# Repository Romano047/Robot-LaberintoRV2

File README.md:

# Robot-LaberintoRV2
Robot Laberinto R 2024-2025

Proyecto realizado en la Escuela de Educación Secundaria Técnica N°5 "2 de Abril" Temperley, Buenos Aires, Argentina. Desarrollado por Iván Romano, estudiante de Electrónica de la institución a cargo del profesor Ing. Martín Leguizamón.

El objetivo de este reoositrio es el de desarrollar un robot autónomo de competición dentro de la categoría de "Robot Laberinto". 

Se tomarán como referencia en su elaboración las reglas actualmente vigentes (2024) dentro de la Liga Nacional de Robótica (LNR) en la categoría de "Laberinto". 

# Guía de Repositorio

- Hardware
  - KiCad: En ella se encuentran todos los archivos correspondientes al desarrollo del PCB.

- 3D
  - AutoCad: En esta carpeta se encuentran los archivos correspondientes al diseño 3D en conjunto a sus trazados a formato .stl para facilitar su posterior impresión. 

- Software
  - Ensayos: Ensayos básicos de cada funcionalidad o punto de interés de forma aislada que conforman el robot. (A su vez se encontrarán en el archivos correspondientes al robort de competición provincial "Alita").
  - LaberintoR2_v2: Versión del Software ejecutada actualmente en el robot. 

# Especificaciones

- Software: Desarrollado en C Orientado a Objetos, por medio del uso de VsCode en conjunto a su extensión PlatformIO.
- Desarrollo de PCBs: KiCad 7
- Placa de Desarrollo: Espressif ESP-32 WROOM DEV KIT
- Sensores de proximidad: HC-SR04
- Drivers de Motores: TB6612fng

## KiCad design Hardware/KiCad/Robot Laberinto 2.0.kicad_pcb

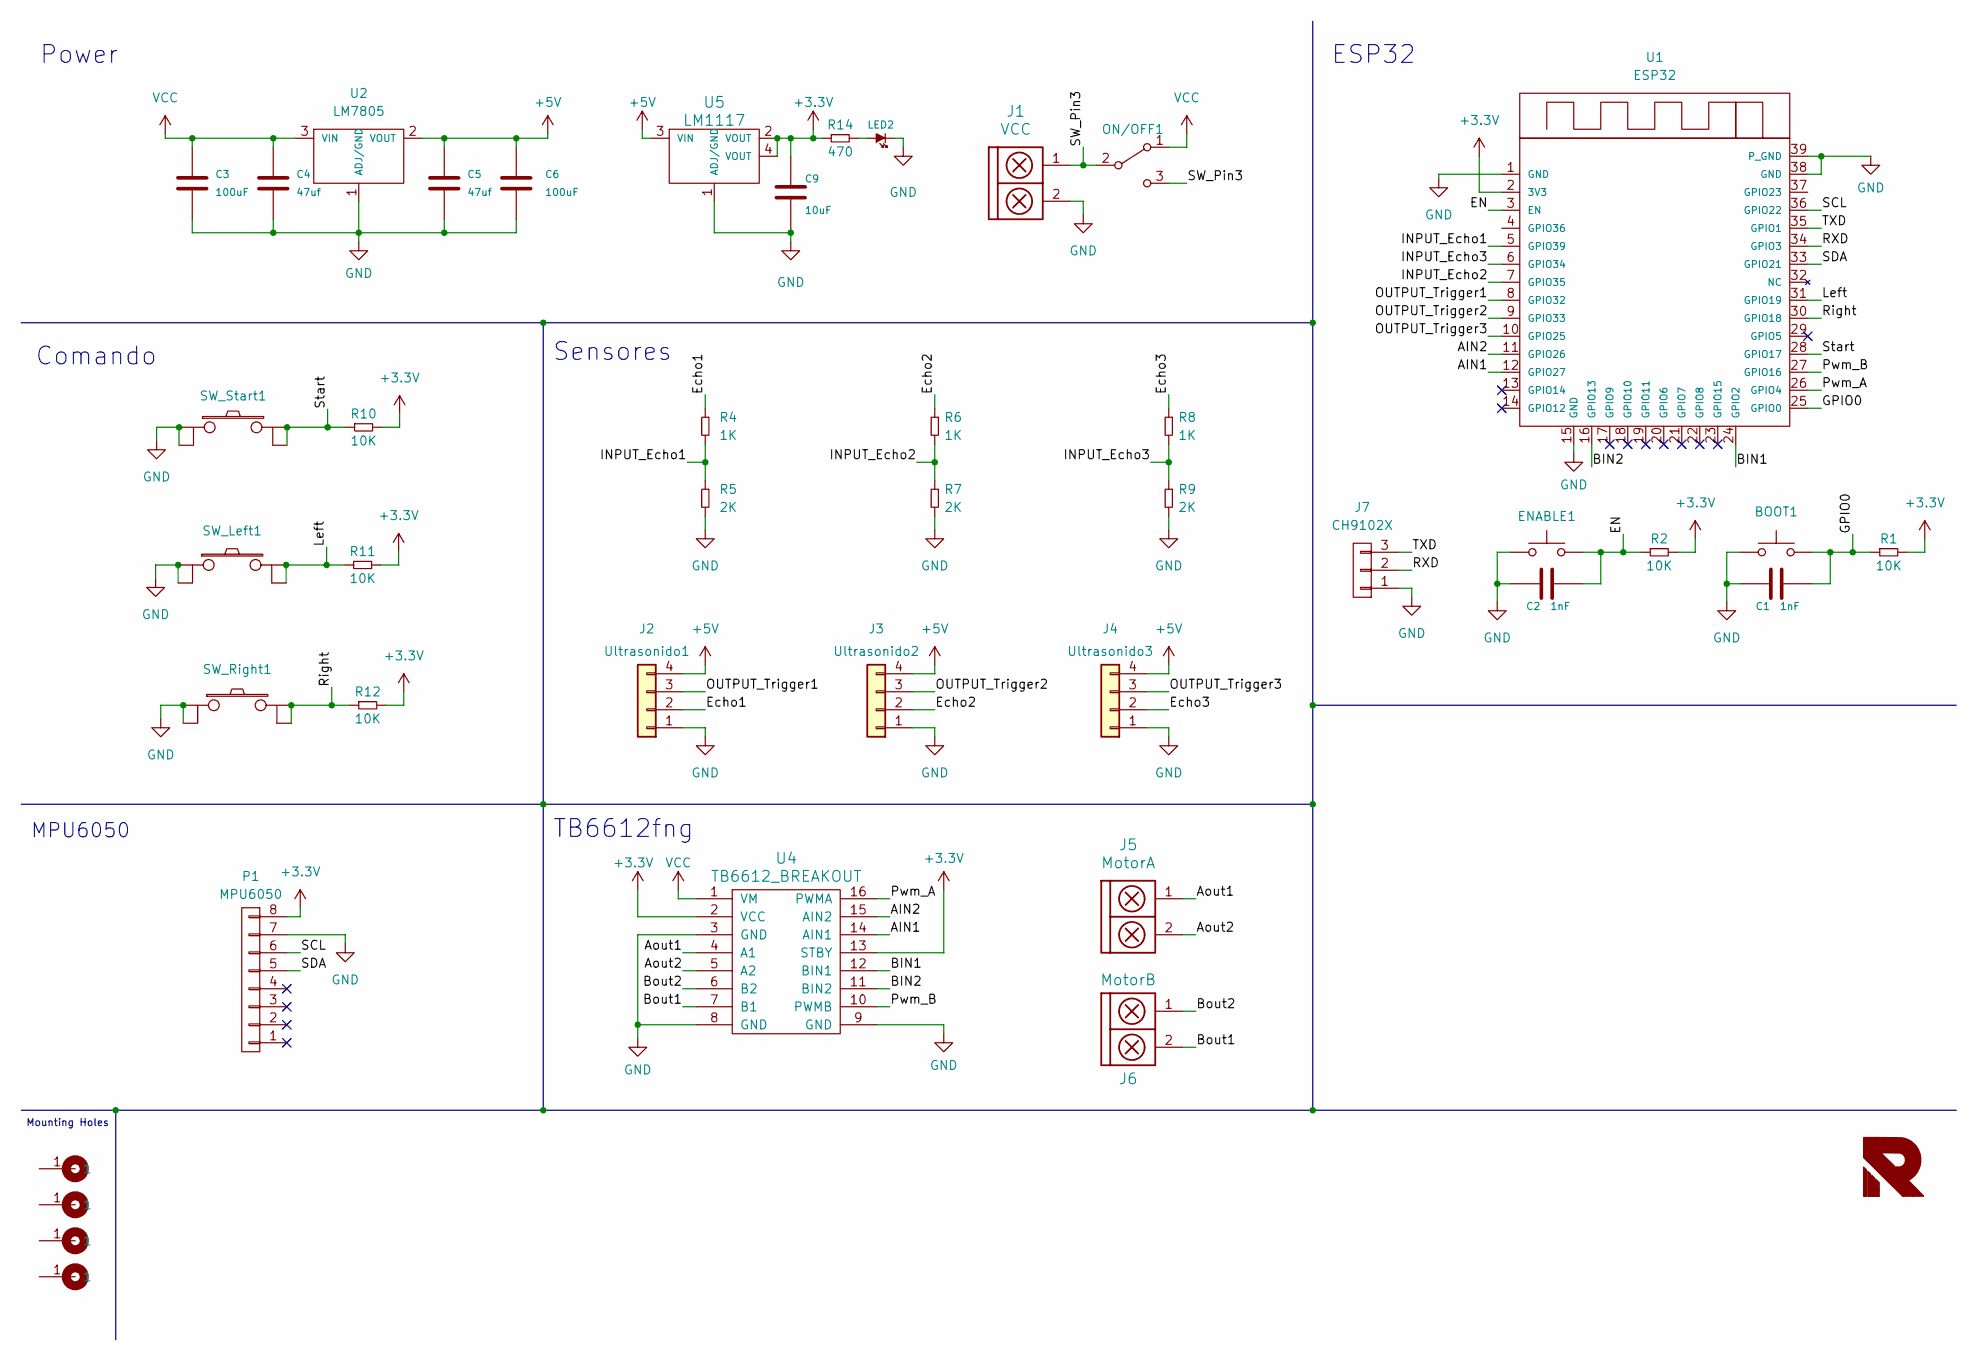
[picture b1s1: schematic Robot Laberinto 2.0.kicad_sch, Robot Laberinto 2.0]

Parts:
BOOT1: SW_Push; SW_SPST_EVQPE1
C1, C2: 1nF; C_0805
C3, C6: 100uF; CAP_ELEC_5x11mm
C4, C5: 47uf; C_0805
C9: 10uF; CAP_ELEC_5x11mm
ENABLE1: SW_Push; SW_SPST_EVQPE1
J1: VCC; BORNERA2_AZUL
J2: Ultrasonido1; pin_strip_4
J3: Ultrasonido2; pin_strip_4
J4: Ultrasonido3; pin_strip_4
J5: MotorA; BORNERA2_AZUL
J6: MotorB; BORNERA2_AZUL
J7: CH9102X; Pin_Strip_3
J8, J9, J10, J11: Cable_PAD; Separador_M3_5mm
LED2: LED; Led_0805
ON/OFF1: SW_SPDT; SW_SPDT_TH_Vertical
P1: MPU6050; Pin_Header_Straight_1x08
R1, R2, R10, R11, R12: 10K; R_0805
R4, R6, R8: 1K; R_0805
R5, R7, R9: 2K; R_0805
R14: 470; R_0805
SW_Left1: SW_PUSH; PUSH_SWITCH_THT
SW_Right1: SW_PUSH; PUSH_SWITCH_THT
SW_Start1: SW_PUSH; PUSH_SWITCH_THT
U1: ESP32; ESP32-WROOM-32_MacroLib
U2: LM7805; TO-220
U4: TB6612_BREAKOUT; TB6612_Breakout
U5: LM1117; SOT223

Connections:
+3.3V: C9.1, P1.8, R1.2, R2.2, R10.2, R11.2, R12.2, R14.1, U1.2 (3V3), U4.2 (VCC), U4.13 (STBY), U5.2 (VOUT), U5.4 (VOUT)
+5V: C5.1, C6.1, J2.4, J3.4, J4.4, U2.2 (VOUT), U5.3 (VIN)
/AIN1: U1.12 (GPIO27), U4.14 (AIN1)
/AIN2: U1.11 (GPIO26), U4.15 (AIN2)
/Aout1: J5.1, U4.4 (A1)
/Aout2: J5.2, U4.5 (A2)
/BIN1: U1.24 (GPIO2), U4.12 (BIN1)
/BIN2: U1.16 (GPIO13), U4.11 (BIN2)
/Bout1: J6.2, U4.7 (B1)
/Bout2: J6.1, U4.6 (B2)
/EN: C2.2, ENABLE1.2, R2.1, U1.3 (EN)
/Echo1: J2.2, R4.1
/Echo2: J3.2, R6.1
/Echo3: J4.2, R8.1
/GPIO0: BOOT1.2, C1.2, R1.1, U1.25 (GPIO0)
/INPUT_Echo1: R4.2, R5.1, U1.5 (GPIO39)
/INPUT_Echo2: R6.2, R7.1, U1.7 (GPIO35)
/INPUT_Echo3: R8.2, R9.1, U1.6 (GPIO34)
/Left: R11.1, SW_Left1.3, SW_Left1.4, U1.31 (GPIO19)
/OUTPUT_Trigger1: J2.3, U1.8 (GPIO32)
/OUTPUT_Trigger2: J3.3, U1.9 (GPIO33)
/OUTPUT_Trigger3: J4.3, U1.10 (GPIO25)
/Pwm_A: U1.26 (GPIO4), U4.16 (PWMA)
/Pwm_B: U1.27 (GPIO16), U4.10 (PWMB)
/RXD: J7.2, U1.34 (GPIO3)
/Right: R12.1, SW_Right1.3, SW_Right1.4, U1.30 (GPIO18)
/SCL: P1.6, U1.36 (GPIO22)
/SDA: P1.5, U1.33 (GPIO21)
/SW_Pin3: J1.1, ON/OFF1.2 (B), ON/OFF1.3 (C)
/Start: R10.1, SW_Start1.3, SW_Start1.4, U1.28 (GPIO17)
/TXD: J7.3, U1.35 (GPIO1)
GND: BOOT1.1, C1.1, C2.1, C3.2, C4.2, C5.2, C6.2, C9.2, ENABLE1.1, J1.2, J2.1, J3.1, J4.1, J7.1, LED2.2 (K), P1.7, R5.2, R7.2, R9.2, SW_Left1.1, SW_Left1.2, SW_Right1.1, SW_Right1.2, SW_Start1.1, SW_Start1.2, U1.1 (GND), U1.15 (GND), U1.38 (GND), U1.39 (P_GND), U2.1 (ADJ/GND), U4.3 (GND), U4.8 (GND), U4.9 (GND), U5.1 (ADJ/GND)
unnamed: LED2.1 (A), R14.2
VCC: C3.1, C4.1, ON/OFF1.1 (A), U2.3 (VIN), U4.1 (VM)

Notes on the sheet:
Sensores
Comando
Mounting Holes
MPU6050
TB6612fng
ESP32
Power

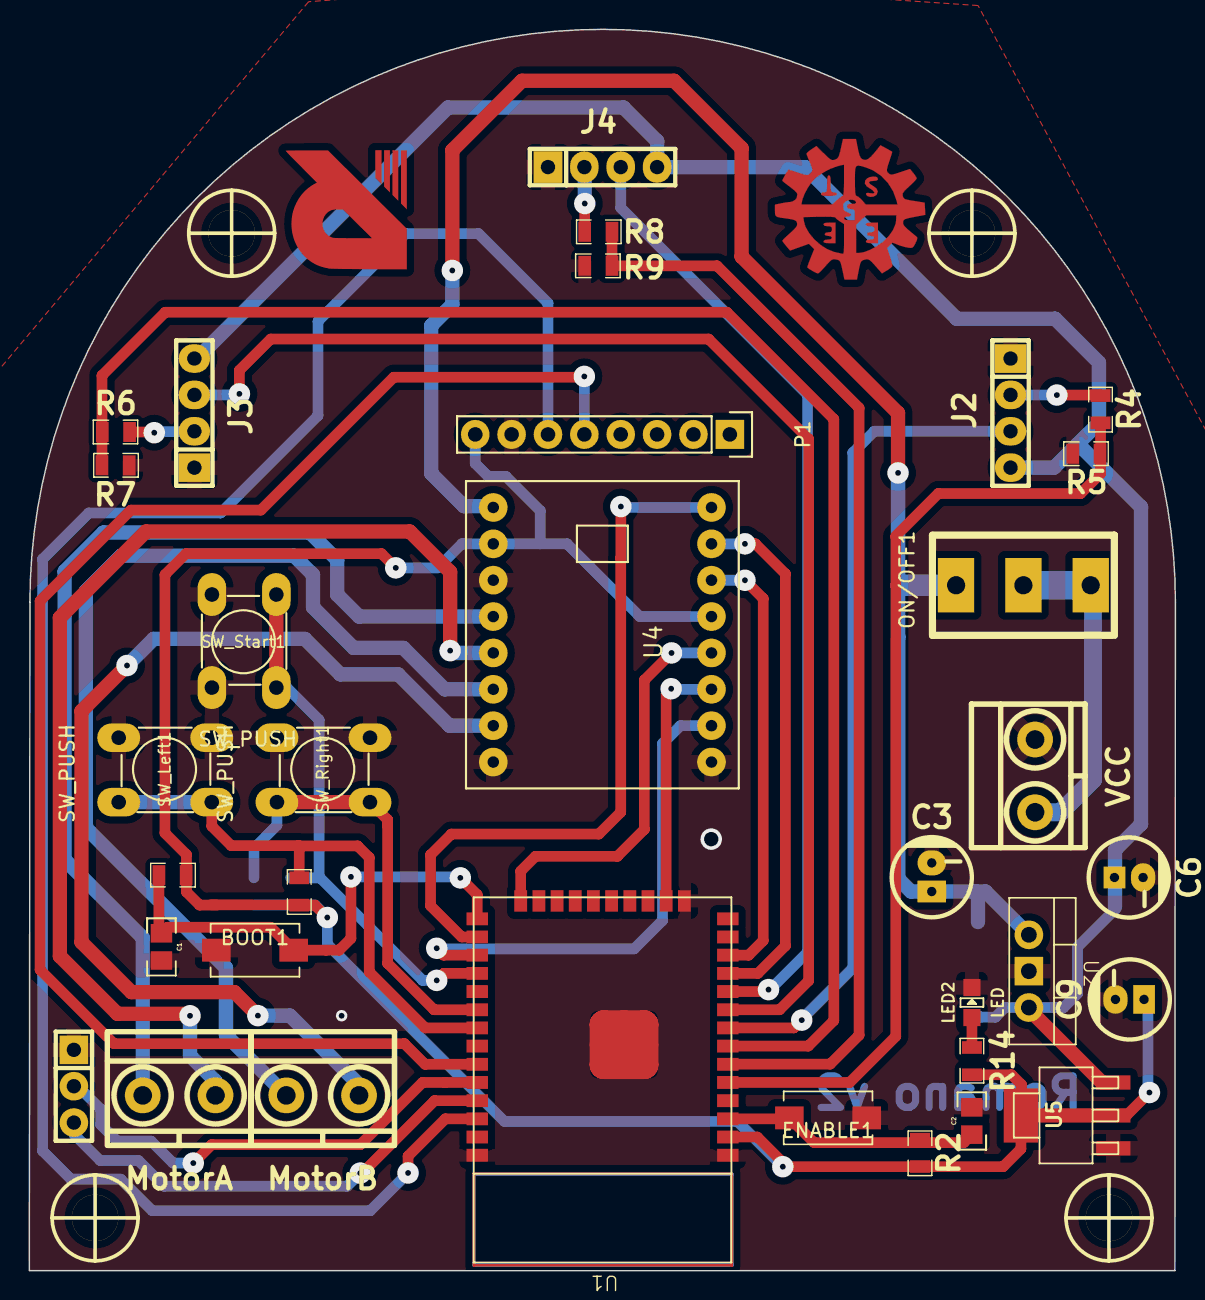
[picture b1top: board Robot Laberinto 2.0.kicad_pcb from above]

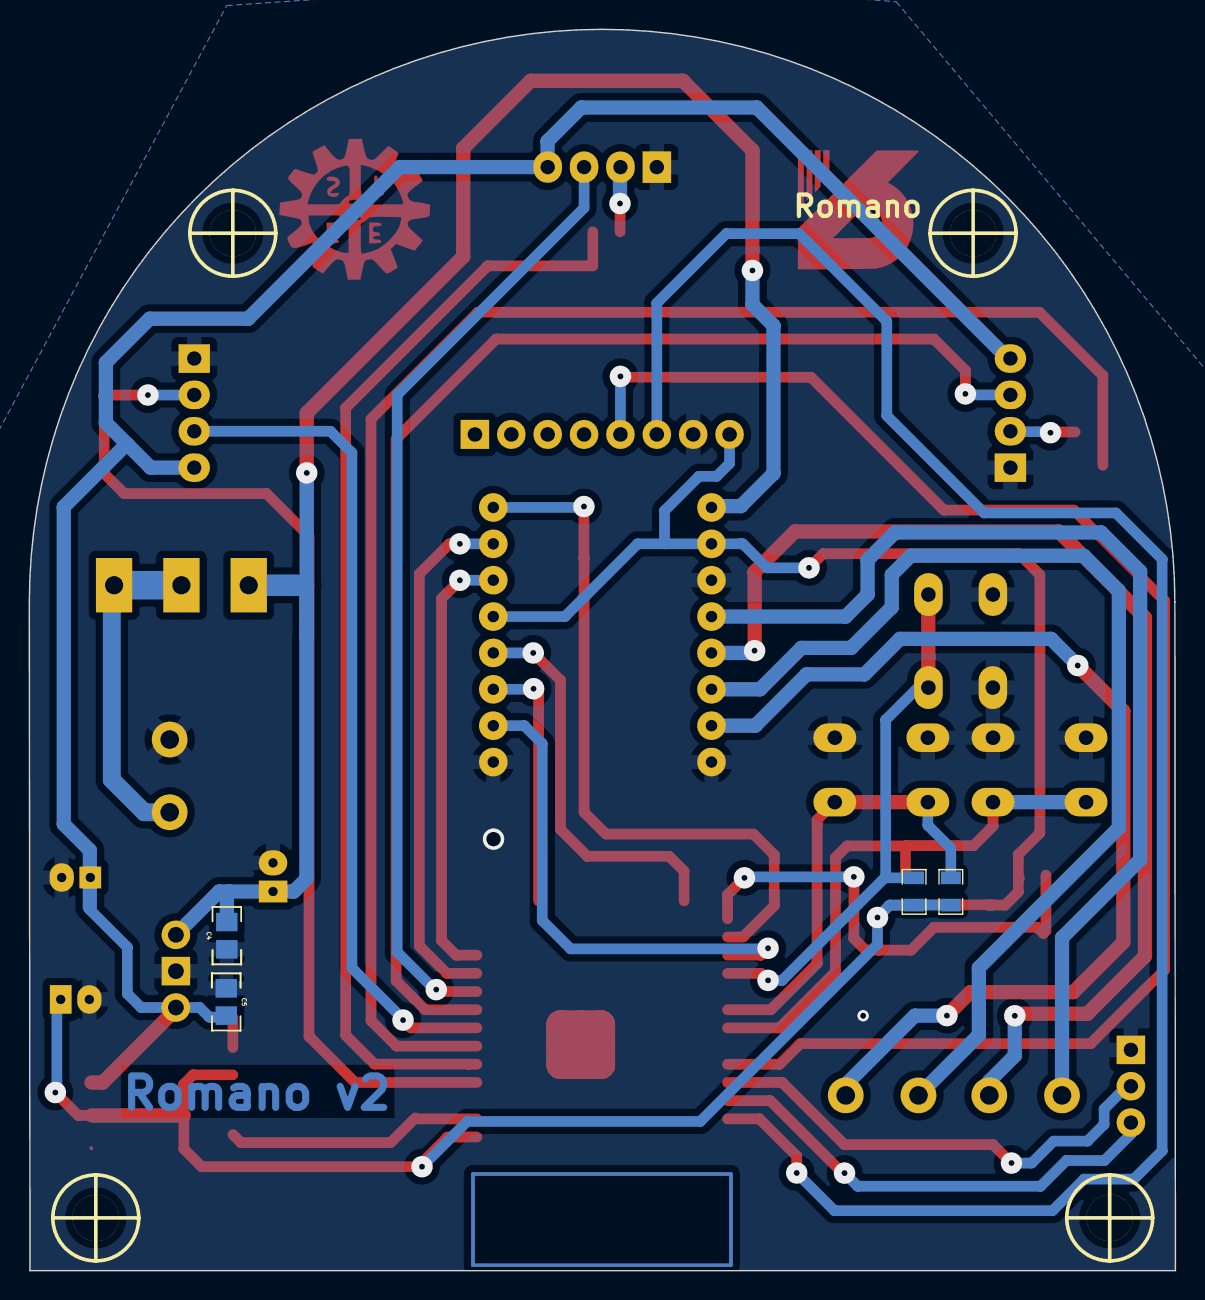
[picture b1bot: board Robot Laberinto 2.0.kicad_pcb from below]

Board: 2 copper layers, 80.0 x 86.7 mm, 43 parts (5 on the bottom side), 34 nets.

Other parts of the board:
Romano: LOGO; LOGO R INVERTIDO

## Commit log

2025-06-30 Update 2025
2025-07-13 motors_TB6612fng
2025-07-14 Actualización Software Osciloscopio
2025-08-08 BETA 1
2025-09-02 Software Update NO MPU
2025-09-06 Software Update
2025-09-12 Code Update
2025-09-13 Software Garín
2025-10-03 Crash Update
